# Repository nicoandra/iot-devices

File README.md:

# iot-devices
IOT schematics, PCBs and Yamls

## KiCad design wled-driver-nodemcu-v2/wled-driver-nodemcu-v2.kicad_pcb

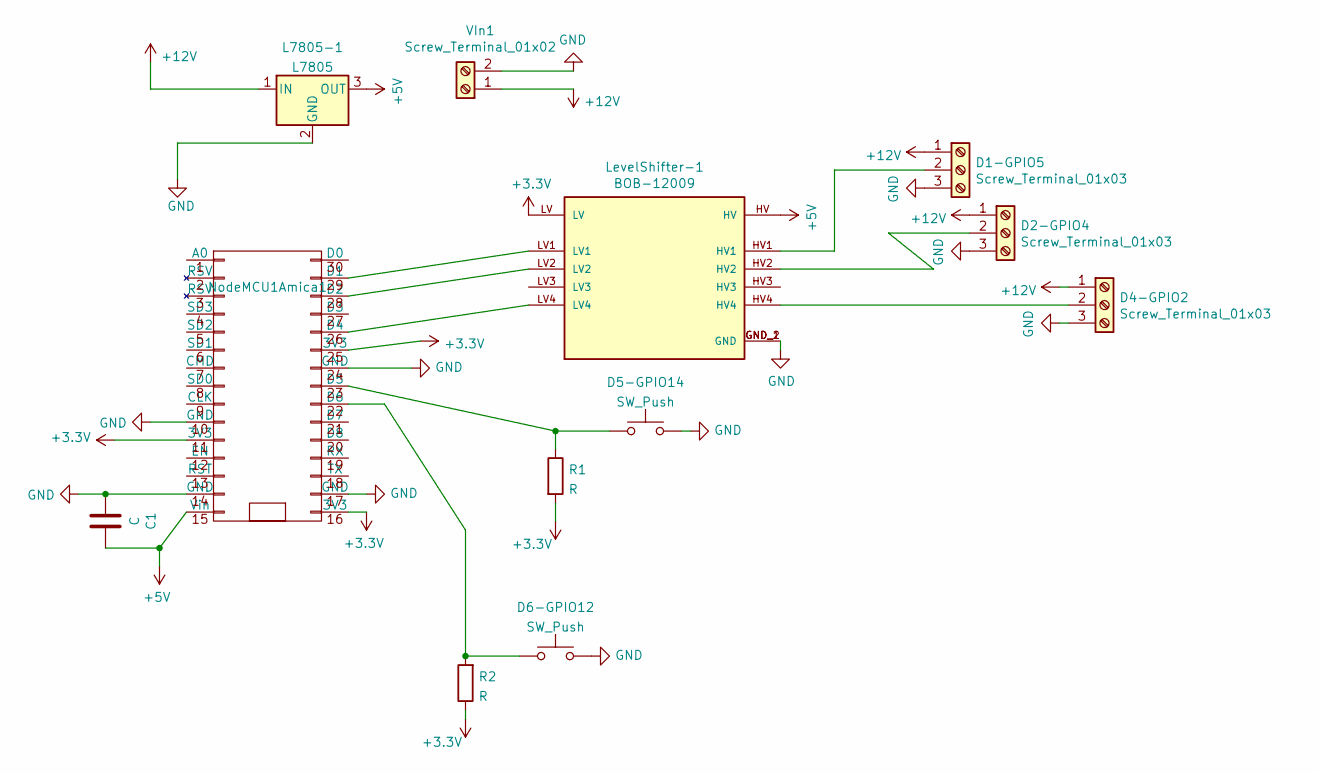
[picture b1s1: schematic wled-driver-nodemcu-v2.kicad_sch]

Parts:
C1: C; CP_Radial_D10.0mm_P5.00mm
D1-GPIO5, D2-GPIO4, D4-GPIO2: Screw_Terminal_01x03; TerminalBlock_Philmore_TB133_1x03_P5.00mm_Horizontal
D5-GPIO14, D6-GPIO12: SW_Push; SW_PUSH_6mm_H4.3mm
L7805-1: L7805; TO-220-3_Horizontal_TabDown
LevelShifter-1: BOB-12009; CONV_BOB-12009; PARTREV 01
NodeMCU1Amica1: NodeMCU_Amica_R2
R1, R2: R; R_Axial_DIN0204_L3.6mm_D1.6mm_P5.08mm_Horizontal
VIn1: Screw_Terminal_01x02; TerminalBlock_Philmore_TB132_1x02_P5.00mm_Horizontal

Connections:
+3V3: LevelShifter-1.LV, NodeMCU1Amica1.11 (3V3), NodeMCU1Amica1.16 (3V3), NodeMCU1Amica1.25 (3V3), R1.2, R2.1
+5V: C1.1, L7805-1.3 (OUT), LevelShifter-1.HV, NodeMCU1Amica1.15 (Vin); also elsewhere on the board
+12V: D1-GPIO5.1, D2-GPIO4.1, D4-GPIO2.1, L7805-1.1 (IN), VIn1.1; also elsewhere on the board
GND: C1.2, D1-GPIO5.3, D2-GPIO4.3, D4-GPIO2.3, D5-GPIO14.2, D6-GPIO12.2, L7805-1.2 (GND), LevelShifter-1.GND_1 (GND), LevelShifter-1.GND_2 (GND), NodeMCU1Amica1.10 (GND), NodeMCU1Amica1.14 (GND), NodeMCU1Amica1.17 (GND), NodeMCU1Amica1.24 (GND), VIn1.2; also elsewhere on the board
unnamed: D1-GPIO5.2, LevelShifter-1.HV1
unnamed: D2-GPIO4.2, LevelShifter-1.HV2
unnamed: D4-GPIO2.2, LevelShifter-1.HV4
unnamed: D5-GPIO14.1, NodeMCU1Amica1.23 (D5), R1.1
unnamed: D6-GPIO12.1, NodeMCU1Amica1.22 (D6), R2.2
unnamed: LevelShifter-1.LV1, NodeMCU1Amica1.29 (D1)
unnamed: LevelShifter-1.LV2, NodeMCU1Amica1.28 (D2)
unnamed: LevelShifter-1.LV4, NodeMCU1Amica1.26 (D4)

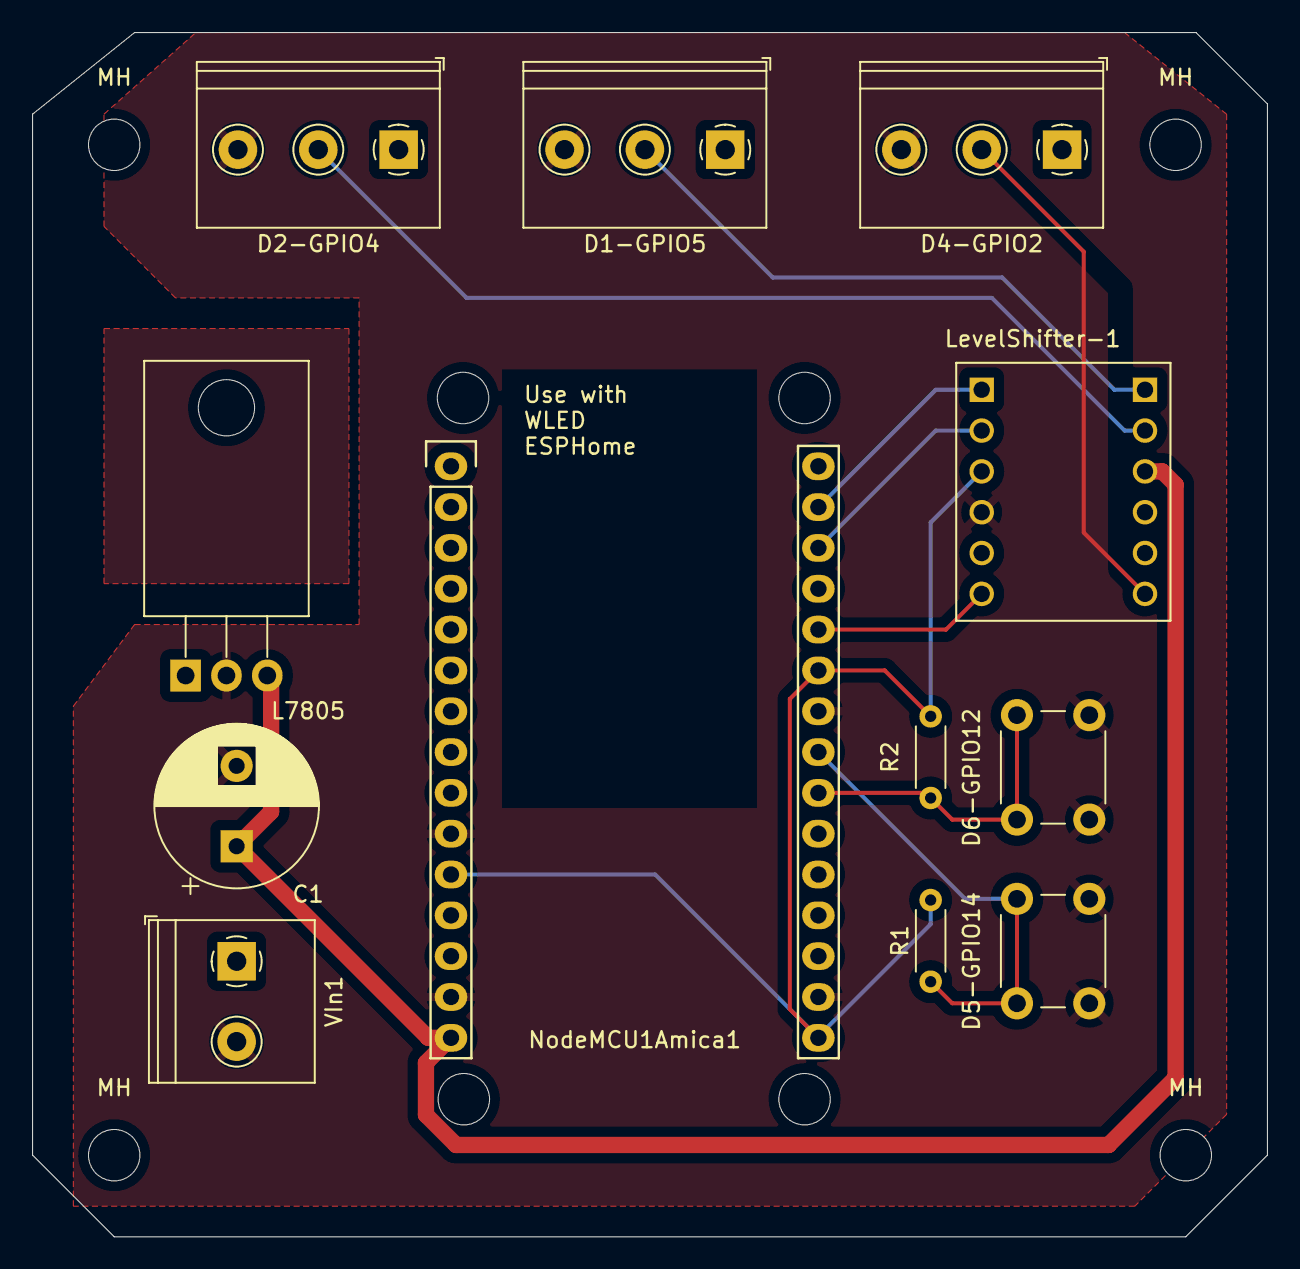
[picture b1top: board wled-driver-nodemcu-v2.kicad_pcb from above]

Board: 2 copper layers, 76.8 x 74.9 mm, 16 parts (0 on the bottom side), 12 nets.

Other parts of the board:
L7805: L7805; TO-220-3_Horizontal_TabDown
MH: MountingHole_3.2mm_M3
MH#2, MH#3, MH#4: MountingHole_3.2mm_M3

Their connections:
+5V: L7805.3 (OUT); also elsewhere on the board
+12V: L7805.1 (IN); also elsewhere on the board
GND: L7805.2 (GND); also elsewhere on the board

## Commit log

2022-01-15 adds schemas and pcb
2022-01-15 adds gitignore
2022-01-15 deletes
